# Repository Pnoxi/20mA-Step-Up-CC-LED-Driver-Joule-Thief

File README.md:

# 20mA-Step-Up-CC-LED-Driver-Joule-Thief-

Documentation
--------------------

https://hackaday.io/project/164471-small-constant-current-20ma-joule-thief

Donate
--------------------

Do you like my work? [Let me know about it and support my other projects!](https://www.patreon.com/pnoxi)

Or just drink beer on my honor :wink:

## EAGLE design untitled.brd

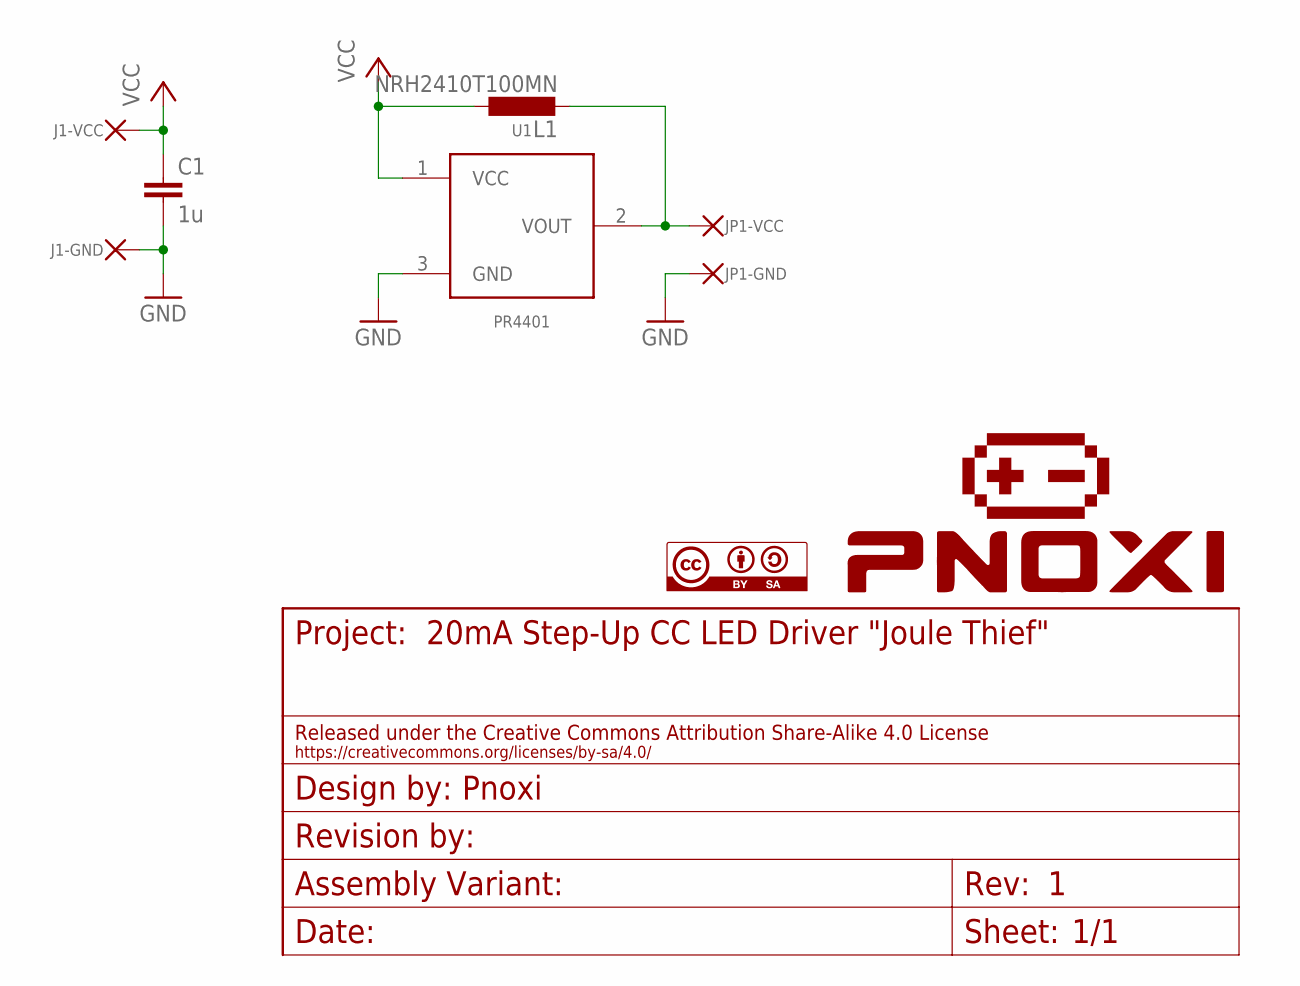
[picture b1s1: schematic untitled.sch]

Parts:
C1: 1u; 0603
J1: SMD_PAD2; SMD_PAD_2
JP1: SMD_PAD2; SMD_PAD_2
L1: NRH2410T100MN; WALSIN_2.4X2.4X1MM
U1: PR4401; SOT23-3

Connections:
GND: C1.2, J1.GND, J1.GND1, J1.GND2, J1.GND3, JP1.GND, JP1.GND1, JP1.GND2, JP1.GND3, U1.3 (GND)
unnamed: JP1.VCC, JP1.VCC1, JP1.VCC2, JP1.VCC3, L1.P$2 (2), U1.2 (VOUT)
VCC: C1.1, J1.VCC, J1.VCC1, J1.VCC2, J1.VCC3, L1.P$1 (1), U1.1 (VCC)

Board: 2 copper layers, 5 parts (0 on the bottom side), 3 nets, no tracks yet.

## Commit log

2019-06-23 Added Design Files!

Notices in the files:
parts and their libraries:
Emsit-Frames: Released under the Creative Commons Attribution Share-Alike 4.0 License
Emsit-Frames: https://creativecommons.org/licenses/by-sa/4.0
